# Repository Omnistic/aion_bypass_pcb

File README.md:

# PCB Design for Hardware Control of Confocal.nl AION in Bypass Mode
## Important Notes ⚠️
- **Current progress**: the board has been designed, printed, assembled, and tested on its own. The controller has also been tested on our microscope successfully. Using the `SELECT` line, one can either use the AION (Confocal.nl) or a FRAP/TIRF module with the AION in bypass mode.
- Floating (digital) inputs should be avoided in a channel that is actively used. I had the case when testing the board, if I only wired one input, the other floating (not wired) input could be `HIGH`.
- When testing the board, the capacitor value changes depending on how many have been soldered to the board already. If a single capacitor is soldered to the board, a multi-meter should still read 100nF. When two capacitors are soldered to the board, and one measures the value of one capacitor, it indicates 200nF. That is because the capacitors are effectively in parallel and their value adds up. With all four capacitors soldered to the board, they should all read 400nF.
## Problem
The AION microscope is controlled by Confocal.nl's own controller. The Confocal.nl controller can also be controlled by the Inscoper Device Controller. The Inscoper Device Controller can control other devices as well. For this reason, the AION can be set into an _optical bypass mode_, which allows accessing the cameras through the AION without making use of the ReScan, to instead perform other kinds of microscopy. However, the cameras and the laser lines (analog and digital) are normally wired to the Confocal.nl controller. This limits the way in which the cameras and the laser lines can be controlled at the level of the Inscoper Device Controller for use in other applications.
## Solution
For two controllers to send signals to the same device, multiplexing is necessary. In the case of the camera trigger (digital) signal, it is not possible to simply use a T-connector because if one controller is high and the other is low a large short-circuit current would flow directly between the two controllers' outputs as they fight each other, potentially damaging the controllers, while the shared node would sit at an undefined voltage that the device could not reliably interpret as high or low.
## Requirements
**⚠️ Those are for my particular case, please check the documentation of your devices accordingly.**
### Devices To Multiplex
#### Oxxius L6Cc With 4 Laser Lines
- 4 digital lines
- 4 analog lines
- Voltage Range (analog and digital): 0-5V
- Input Impedance (analog and digital): 500Ω
#### 2x Kinetix (10Mpix Version)
- 2 digital lines (Trigger In) / 1 per camera
- Voltage Range: 0-5V
- Input Impedance: Unknown
  - For reference, a similar ORCA-Fusion BT has an impedance of 10kΩ
### Selected ICs
#### Digital Multiplexing
`SN74HC157N` is a 4 x 2:1 digital multiplexer, with a single `SELECT` bit. Two will be used for a total of 8 (2:1) digital channels. Although only 6 are required.
#### Analog Multiplexing
`CD74HC4053E` is 3 x 2:1 analog multiplexer, with three `SELECT` bits (1 per channel). Two will be used for a total of 6 (2:1) analog channels. Although only 4 are required.
### PCB Design Rationale
Assuming up to two lasers are operated simultaneously, the current drawn from 2 digital and 2 analog lines is 40mA. On top of that, the two cameras only contribute 1mA (assuming 10kΩ). Multiplying by a safety factor of 1.2 that is about 50mA. The power will be supplied to the board via the Inscoper Device Controller directly.

All the `SELECT` bits are common and a single `SELECT` signal is also taken from the Inscoper Device Controller. This signal effectively switches between AION control and Inscoper control (for the cameras and lasers).

The `SELECT` line is pulled down by a 10kΩ resistor, defaulting to LOW, which corresponds to AION (for my use case).

Only the `SELECT` crosses the PCB with minimal length in the back face to keep continuous ground zone.

100nF capacitors are used on each IC for decoupling.

Vertical through-hole SMA connectors will be soldered to the PCB. The PCB will be mounted in a case and a front panel will have SMA (inside facing) to SMB (outside facing) connectors. Minimum distance between SMA connectors optimized for accessible mounting.

## Overview

## Realization
- Printed by JLCPCB for about 32USD (5xPCBs = 18USD + shipping = 14USD)
- Soldered manually
- We have a local electronics workshop and I'm not sure if the price are truly accurate to the market but here is a small cost breakdown:
  - **32x SMA connectors = 256USD**
  - 4x 16-pin sockets = 1USD
  - 2x SN74HC157N = 2.2USD (bought from DigiKey)
  - 2x CD74HC4053E = 1.3USD (bought from DigiKey)
  - 4x 100nF = 0.25USD
  - 1x 10kΩ = 0.05USD

## Enclosure
- 1x Enclosure [1401E (Hammond)](https://www.hammfg.com/electronics/small-case/general-purpose/1401) = 110USD
- 32x SMA-Bulkhead cable [794-2885 (RS PRO)](https://uk.rs-online.com/web/p/coaxial-cable/7942885?gb=a) = 640USD

Note: I originally ordered SMA-Bulkhead cables that were thicker (not intentionally) but they sent only a few and the others were on back order. I cancelled the order and got those above that are thinner. The reason I say this is because it is easier to assemble with the thin cables imo. And also, I am sorry for the poor cable management... The enclosure foot print is perhaps a tiny bit too small but it works.

## Acknowledgements
We thank Alfonso Fontao Blanco from the [Microelectronics Design Center (ETHZ)](https://dz.ethz.ch/) for kindly reviewing the design and suggesting minor improvements (more distance between SMA connectors, mounting holes, shorter `SELECT` line on the back face).

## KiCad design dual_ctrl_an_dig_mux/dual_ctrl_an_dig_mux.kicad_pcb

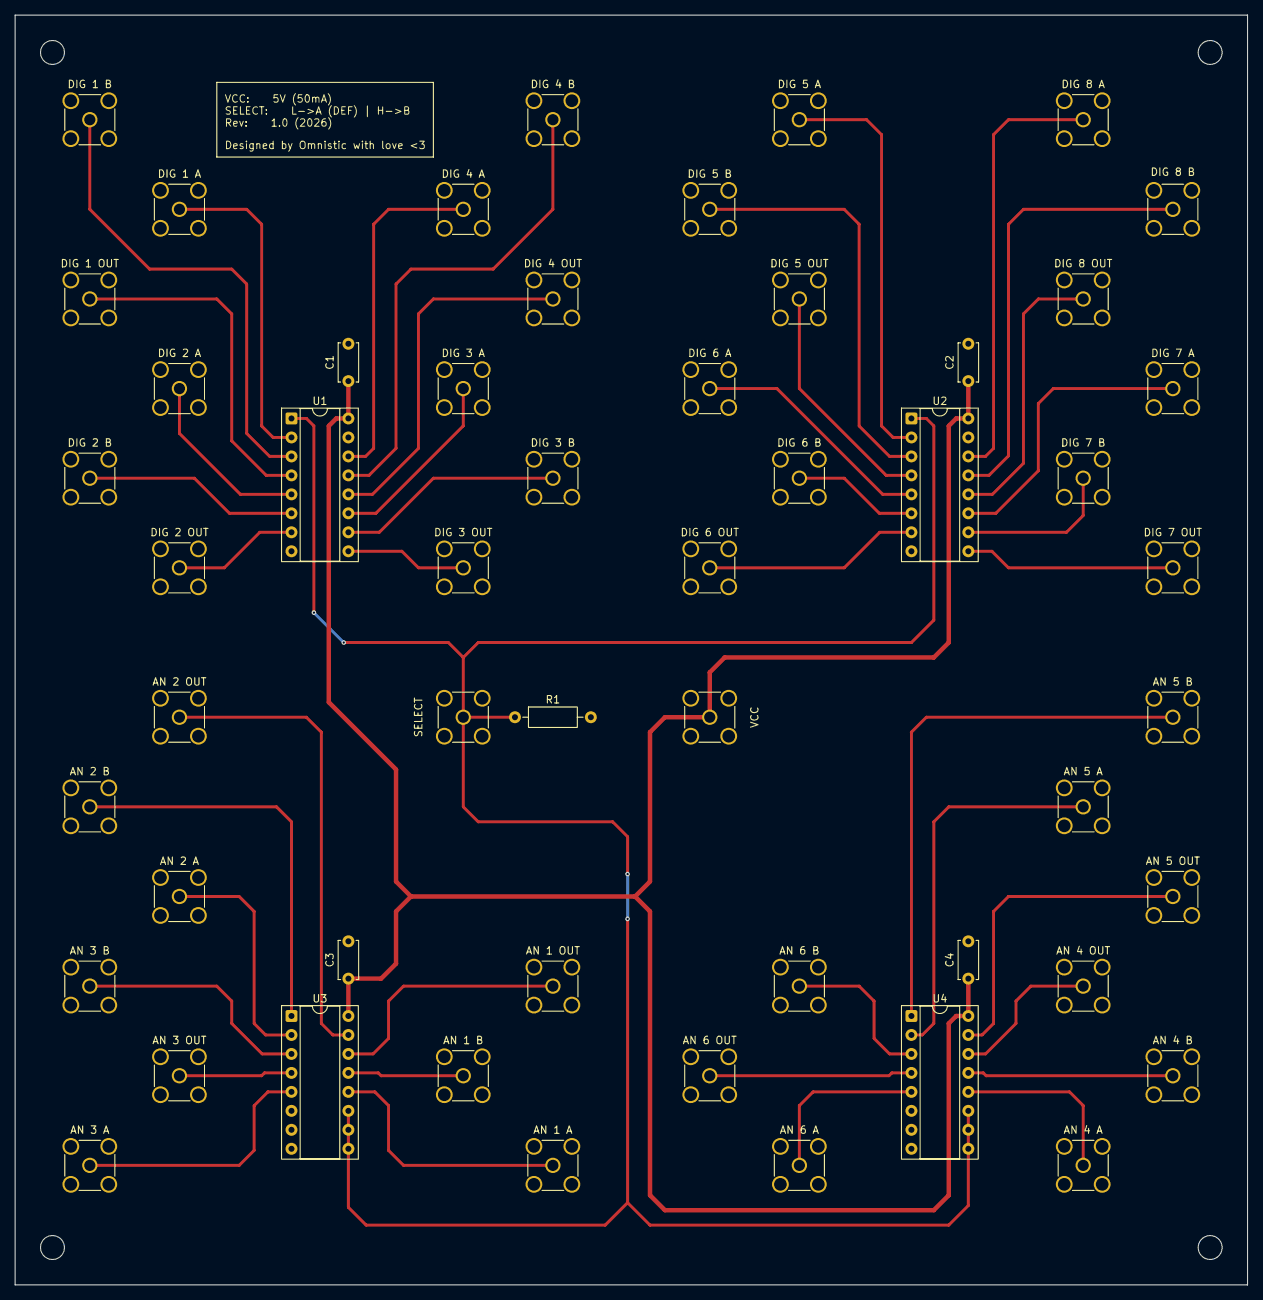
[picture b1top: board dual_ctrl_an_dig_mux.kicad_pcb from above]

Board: 2 copper layers, 165.0 x 170.0 mm, 53 parts (0 on the bottom side), 45 nets.

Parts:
AN 1 A, AN 1 B, AN 1 OUT, AN 2 A, AN 2 B, AN 2 OUT, AN 3 A, AN 3 B, AN 3 OUT, AN 4 A, AN 4 B, AN 4 OUT, AN 5 A, AN 5 B, AN 5 OUT, AN 6 A, AN 6 B, AN 6 OUT: Conn_Coaxial; SMA_Amphenol_901-144_Vertical
C1, C2, C3, C4: 100nF; C_Disc_D5.0mm_W2.5mm_P5.00mm
DIG 1 A, DIG 1 B, DIG 1 OUT, DIG 2 A, DIG 2 B, DIG 2 OUT, DIG 3 A, DIG 3 B, DIG 3 OUT, DIG 4 A, DIG 4 B, DIG 4 OUT, DIG 5 A, DIG 5 B, DIG 5 OUT, DIG 6 A, DIG 6 B, DIG 6 OUT, DIG 7 A, DIG 7 B, DIG 7 OUT, DIG 8 A, DIG 8 B, DIG 8 OUT: Conn_Coaxial; SMA_Amphenol_901-144_Vertical
R1: 10k; R_Axial_DIN0207_L6.3mm_D2.5mm_P10.16mm_Horizontal
SELECT: Conn_Coaxial; SMA_Amphenol_901-144_Vertical
U1, U2: 74HC157; DIP-16_W7.62mm_Socket
U3, U4: 74HC4053; DIP-16_W7.62mm_Socket
VCC: Conn_Coaxial; SMA_Amphenol_901-144_Vertical

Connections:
GND: AN 1 A.2 (Ext), AN 1 B.2 (Ext), AN 1 OUT.2 (Ext), AN 2 A.2 (Ext), AN 2 B.2 (Ext), AN 2 OUT.2 (Ext), AN 3 A.2 (Ext), AN 3 B.2 (Ext), AN 3 OUT.2 (Ext), AN 4 A.2 (Ext), AN 4 B.2 (Ext), AN 4 OUT.2 (Ext), AN 5 A.2 (Ext), AN 5 B.2 (Ext), AN 5 OUT.2 (Ext), AN 6 A.2 (Ext), AN 6 B.2 (Ext), AN 6 OUT.2 (Ext), C1.2, C2.2, C3.2, C4.2, DIG 1 A.2 (Ext), DIG 1 B.2 (Ext), DIG 1 OUT.2 (Ext), DIG 2 A.2 (Ext), DIG 2 B.2 (Ext), DIG 2 OUT.2 (Ext), DIG 3 A.2 (Ext), DIG 3 B.2 (Ext), DIG 3 OUT.2 (Ext), DIG 4 A.2 (Ext), DIG 4 B.2 (Ext), DIG 4 OUT.2 (Ext), DIG 5 A.2 (Ext), DIG 5 B.2 (Ext), DIG 5 OUT.2 (Ext), DIG 6 A.2 (Ext), DIG 6 B.2 (Ext), DIG 6 OUT.2 (Ext), DIG 7 A.2 (Ext), DIG 7 B.2 (Ext), DIG 7 OUT.2 (Ext), DIG 8 A.2 (Ext), DIG 8 B.2 (Ext), DIG 8 OUT.2 (Ext), R1.2, SELECT.2 (Ext), U1.8 (GND), U1.15 (E), U2.8 (GND), U2.15 (E), U3.6 (INH), U3.7 (VEE), U3.8 (VSS), U4.6 (INH), U4.7 (VEE), U4.8 (VSS), VCC.2 (Ext)
unnamed: R1.1, SELECT.1 (In), U1.1 (S), U2.1 (S), U3.9 (S3), U3.10 (S2), U3.11 (S1), U4.9 (S3), U4.10 (S2), U4.11 (S1)
unnamed: DIG 2 B.1 (In), U1.6 (I1b)
unnamed: DIG 2 A.1 (In), U1.5 (I0b)
unnamed: DIG 1 B.1 (In), U1.3 (I1a)
unnamed: DIG 1 A.1 (In), U1.2 (I0a)
unnamed: DIG 3 A.1 (In), U1.11 (I0c)
unnamed: DIG 3 B.1 (In), U1.10 (I1c)
unnamed: DIG 4 A.1 (In), U1.14 (I0d)
unnamed: DIG 4 B.1 (In), U1.13 (I1d)
unnamed: DIG 4 OUT.1 (In), U1.12 (Zd)
unnamed: DIG 3 OUT.1 (In), U1.9 (Zc)
unnamed: DIG 2 OUT.1 (In), U1.7 (Zb)
unnamed: DIG 1 OUT.1 (In), U1.4 (Za)
unnamed: DIG 5 A.1 (In), U2.2 (I0a)
unnamed: DIG 5 B.1 (In), U2.3 (I1a)
unnamed: DIG 6 A.1 (In), U2.5 (I0b)
unnamed: DIG 6 B.1 (In), U2.6 (I1b)
unnamed: DIG 7 A.1 (In), U2.11 (I0c)
unnamed: DIG 7 B.1 (In), U2.10 (I1c)
unnamed: DIG 8 A.1 (In), U2.14 (I0d)
unnamed: DIG 8 B.1 (In), U2.13 (I1d)
unnamed: DIG 5 OUT.1 (In), U2.4 (Za)
unnamed: DIG 6 OUT.1 (In), U2.7 (Zb)
unnamed: DIG 7 OUT.1 (In), U2.9 (Zc)
unnamed: DIG 8 OUT.1 (In), U2.12 (Zd)
unnamed: AN 3 OUT.1 (In), U3.4 (C)
unnamed: AN 2 OUT.1 (In), U3.15 (B)
unnamed: AN 1 OUT.1 (In), U3.14 (A)
unnamed: AN 4 OUT.1 (In), U4.14 (A)
unnamed: AN 5 OUT.1 (In), U4.15 (B)
unnamed: AN 6 OUT.1 (In), U4.4 (C)
unnamed: AN 3 B.1 (In), U3.3 (C1)
unnamed: AN 3 A.1 (In), U3.5 (C0)
unnamed: AN 2 B.1 (In), U3.1 (B1)
unnamed: AN 2 A.1 (In), U3.2 (B0)
unnamed: AN 1 B.1 (In), U3.13 (A1)
unnamed: AN 1 A.1 (In), U3.12 (A0)
unnamed: AN 4 A.1 (In), U4.12 (A0)
unnamed: AN 4 B.1 (In), U4.13 (A1)
unnamed: AN 5 A.1 (In), U4.2 (B0)
unnamed: AN 5 B.1 (In), U4.1 (B1)
unnamed: AN 6 A.1 (In), U4.5 (C0)
unnamed: AN 6 B.1 (In), U4.3 (C1)
VCC: C1.1, C2.1, C3.1, C4.1, U1.16 (VCC), U2.16 (VCC), U3.16 (VDD), U4.16 (VDD), VCC.1 (In)
